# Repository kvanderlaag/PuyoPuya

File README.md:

# PuyoPuya
 Puya MCU Protoboard

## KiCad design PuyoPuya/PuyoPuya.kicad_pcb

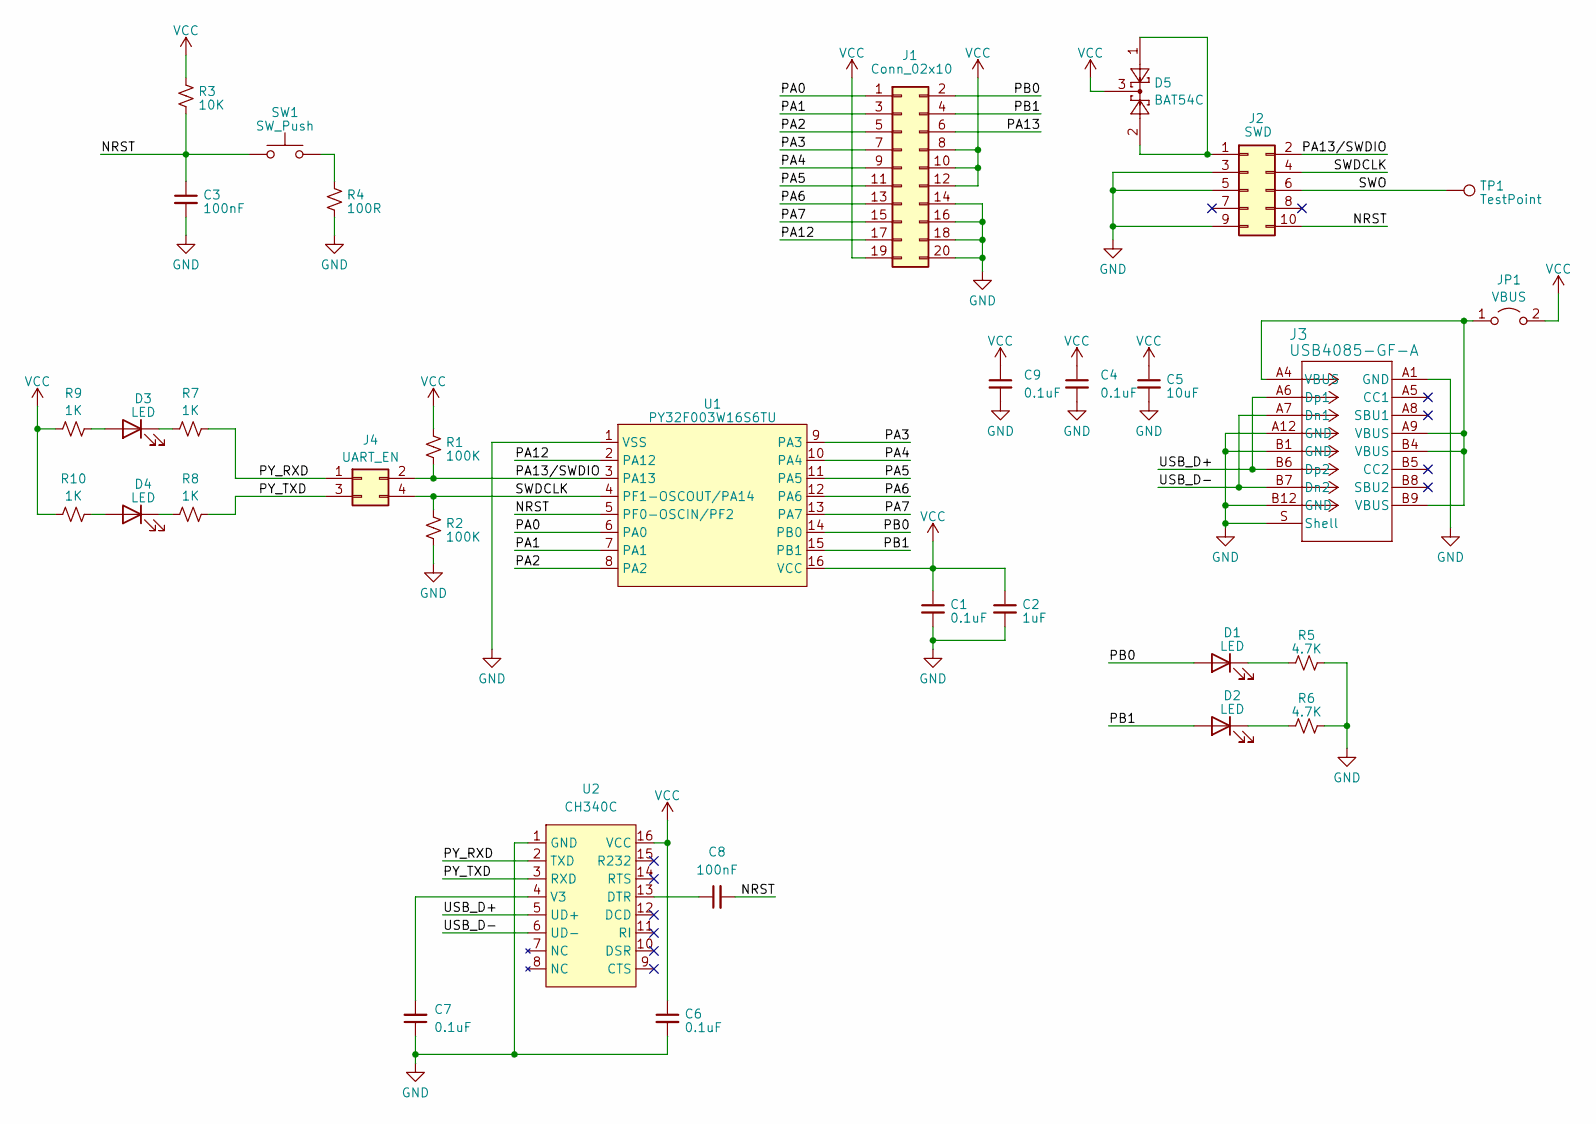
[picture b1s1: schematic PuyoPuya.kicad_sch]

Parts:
C1, C4, C6, C7, C9: 0.1uF; C_0805_2012Metric_Pad1.18x1.45mm_HandSolder
C2: 1uF; C_0805_2012Metric_Pad1.18x1.45mm_HandSolder
C3, C8: 100nF; C_0805_2012Metric_Pad1.18x1.45mm_HandSolder
C5: 10uF; C_0805_2012Metric_Pad1.18x1.45mm_HandSolder
D1, D2, D3, D4: LED; LED_0805_2012Metric_Pad1.15x1.40mm_HandSolder
D5: BAT54C; SOT-23
J1: Conn_02x10; PinSocket_2x10_P2.54mm_Vertical
J2: SWD; PinHeader_2x05_P2.54mm_Vertical
J3: USB4085-GF-A; CONN16_USB4085-GF-A_GCT
J4: UART_EN; PinHeader_2x02_P2.54mm_Vertical
JP1: VBUS; PinHeader_1x02_P2.54mm_Vertical
R1, R2: 100K; R_0805_2012Metric_Pad1.20x1.40mm_HandSolder
R3: 10K; R_0805_2012Metric_Pad1.20x1.40mm_HandSolder
R4: 100R; R_0805_2012Metric_Pad1.20x1.40mm_HandSolder
R5, R6: 4.7K; R_0805_2012Metric_Pad1.20x1.40mm_HandSolder
R7, R8, R9, R10: 1K; R_0805_2012Metric_Pad1.20x1.40mm_HandSolder
SW1: SW_Push; SW4_PTS815 SJM 250 SMTR LFS_CNK
TP1: TestPoint; TestPoint_Pad_D1.5mm
U1: PY32F003W16S6TU; SO-16_3.9x9.9mm_P1.27mm
U2: CH340C; SOP-16_3.9x9.9mm_P1.27mm

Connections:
/NRST: C3.1, C8.2, J2.10, R3.2, SW1.1, U1.5 (PF0-OSCIN/PF2)
/PA0: J1.1, U1.6 (PA0)
/PA1: J1.3, U1.7 (PA1)
/PA2: J1.5, U1.8 (PA2)
/PA3: J1.7, U1.9 (PA3)
/PA4: J1.9, U1.10 (PA4)
/PA5: J1.11, U1.11 (PA5)
/PA6: J1.13, U1.12 (PA6)
/PA7: J1.15, U1.13 (PA7)
/PA12: J1.17, U1.2 (PA12)
/PA13: J1.6
/PA13/SWDIO: J2.2, J4.2, R1.2, U1.3 (PA13)
/PB0: D1.2 (A), J1.2, U1.14 (PB0)
/PB1: D2.2 (A), J1.4, U1.15 (PB1)
/PY_RXD: J4.1, R7.1, U2.2 (TXD)
/PY_TXD: J4.3, R8.1, U2.3 (RXD)
/SWDCLK: J2.4, J4.4, R2.1, U1.4 (PF1-OSCOUT/PA14)
/SWO: J2.6, TP1.1
/USB_D+: J3.A6 (Dp1), J3.B6 (Dp2), U2.5 (UD+)
/USB_D-: J3.A7 (Dn1), J3.B7 (Dn2), U2.6 (UD-)
GND: C1.2, C2.2, C3.2, C4.2, C5.2, C6.2, C7.1, C9.2, J1.14, J1.16, J1.18, J1.20, J2.3, J2.5, J2.9, J3.A1 (GND), J3.A12 (GND), J3.B1 (GND), J3.B12 (GND), J3.S (Shell), R2.2, R4.2, R5.1, R6.1, U1.1 (VSS), U2.1 (GND)
unnamed: D1.1 (K), R5.2
unnamed: D2.1 (K), R6.2
unnamed: D3.2 (A), R9.1
unnamed: D3.1 (K), R7.2
unnamed: D4.2 (A), R10.1
unnamed: D4.1 (K), R8.2
unnamed: D5.1, D5.2, J2.1
unnamed: J3.A4 (VBUS), J3.A9 (VBUS), J3.B4 (VBUS), J3.B9 (VBUS), JP1.1 (A)
unnamed: R4.1, SW1.2
unnamed: C8.1, U2.13 (DTR)
unnamed: C7.2, U2.4 (V3)
VCC: C1.1, C2.1, C4.1, C5.1, C6.1, C9.1, D5.3, J1.8, J1.10, J1.12, J1.19, JP1.2 (B), R1.1, R3.1, R9.2, R10.2, U1.16 (VCC), U2.16 (VCC)

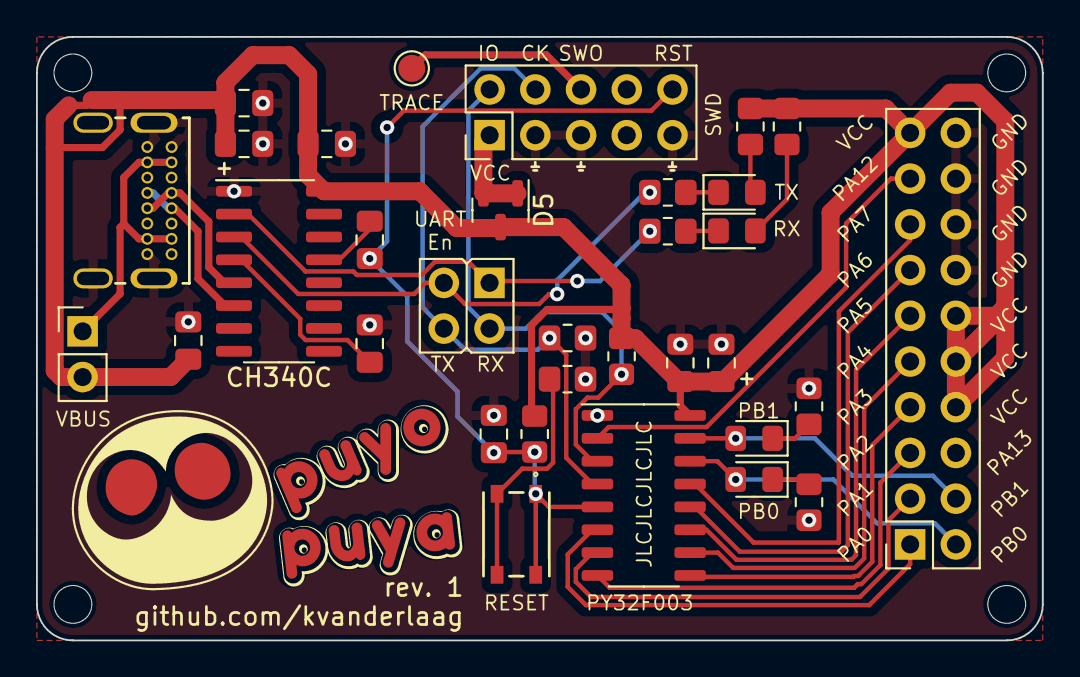
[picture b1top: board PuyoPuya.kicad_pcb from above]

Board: 2 copper layers, 55.9 x 33.5 mm, 33 parts (0 on the bottom side), 32 nets.

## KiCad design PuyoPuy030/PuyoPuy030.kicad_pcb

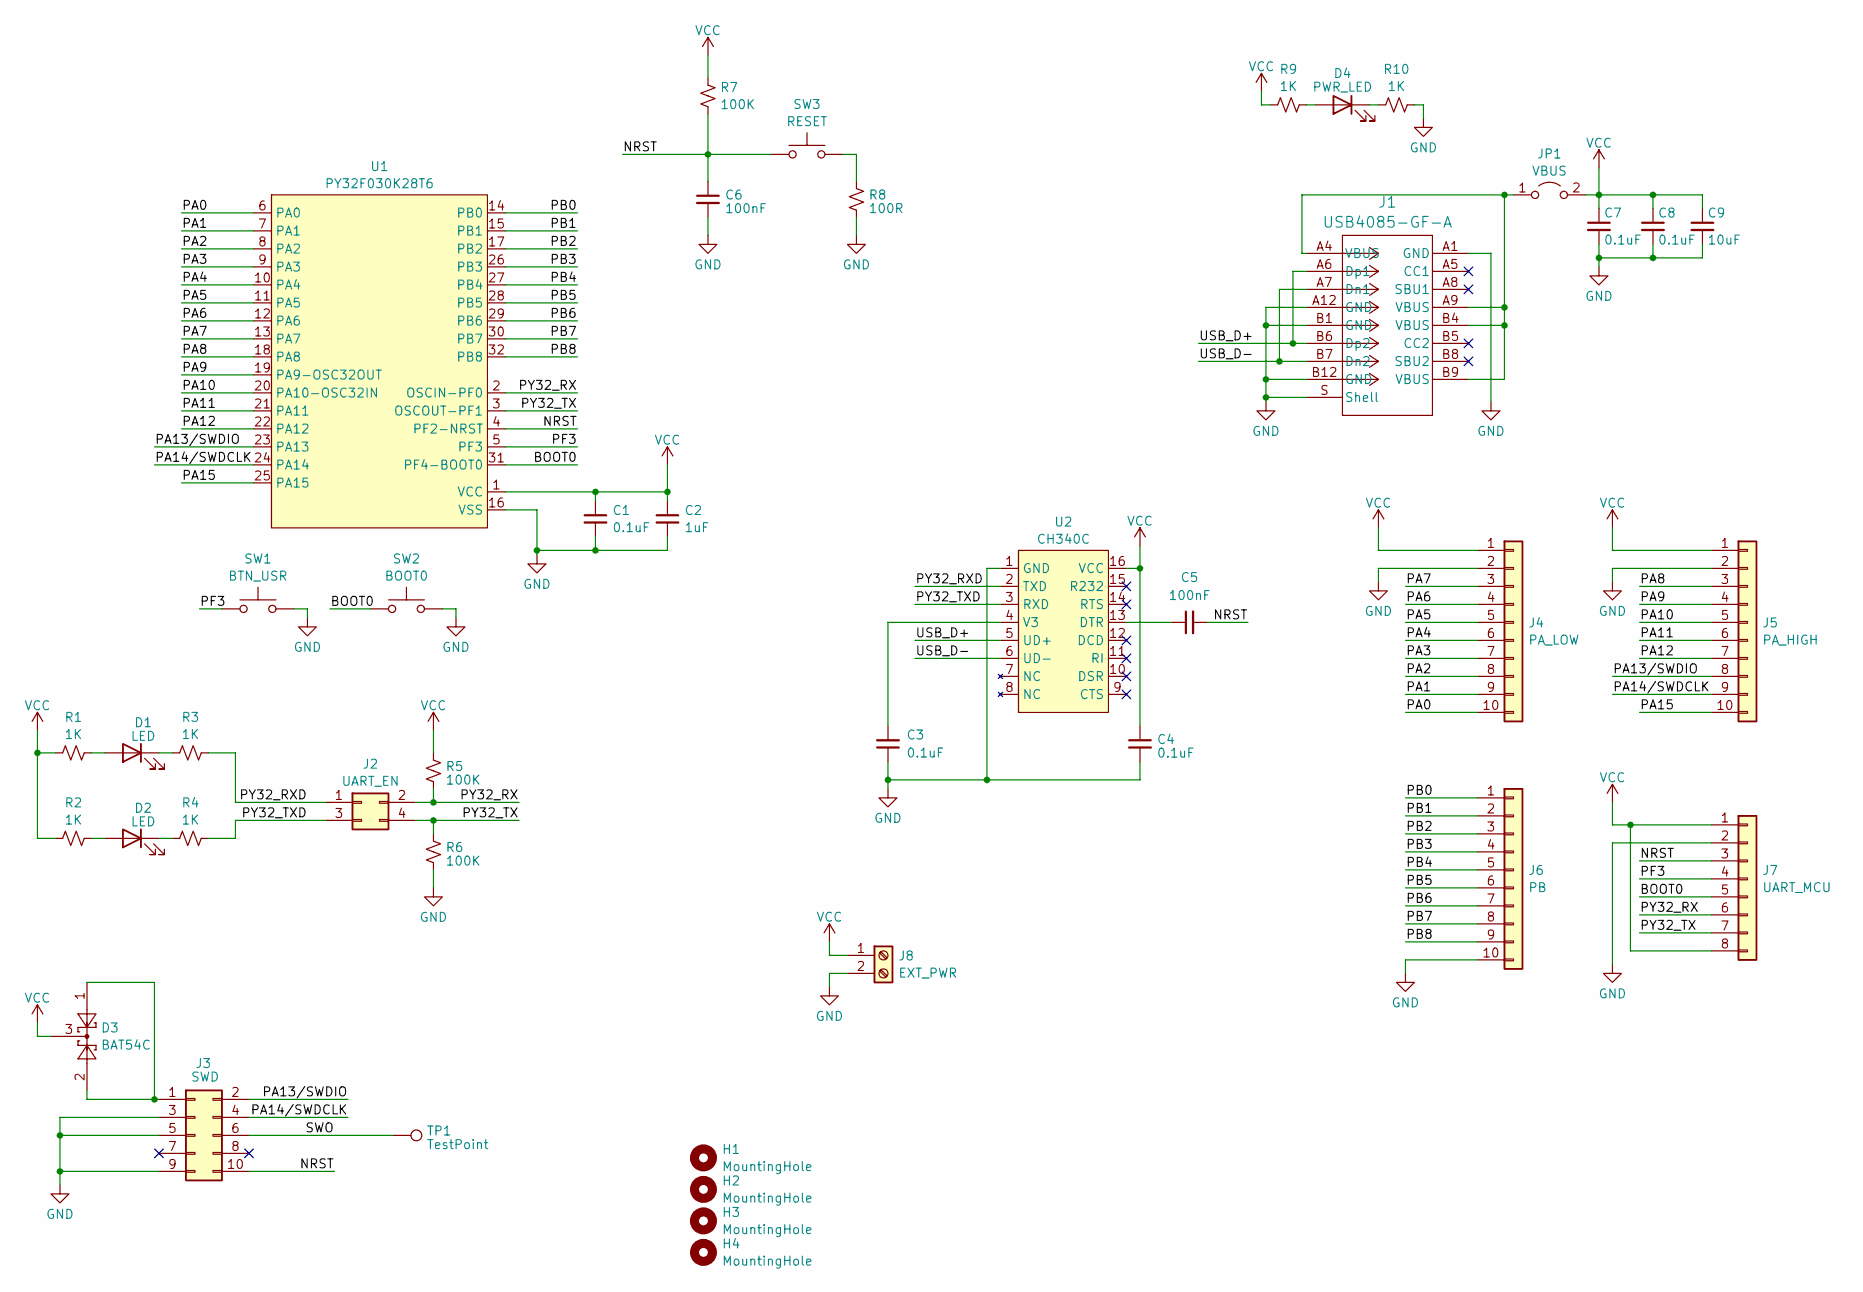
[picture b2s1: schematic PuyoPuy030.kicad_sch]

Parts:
C1, C3, C4, C7, C8: 0.1uF; C_0805_2012Metric
C2: 1uF; C_0805_2012Metric
C5, C6: 100nF; C_0805_2012Metric
C9: 10uF; C_0805_2012Metric
D1, D2: LED; LED_0805_2012Metric_Pad1.15x1.40mm_HandSolder
D3: BAT54C; SOT-23
D4: PWR_LED; LED_0805_2012Metric_Pad1.15x1.40mm_HandSolder
H1, H2, H3, H4: MountingHole; MountingHole_2.2mm_M2
J1: USB4085-GF-A; CONN16_USB4085-GF-A_GCT
J2: UART_EN; PinHeader_2x02_P2.54mm_Vertical
J3: SWD; PinHeader_2x05_P2.54mm_Vertical
J4: PA_LOW; PinSocket_1x10_P2.54mm_Vertical
J5: PA_HIGH; PinSocket_1x10_P2.54mm_Vertical
J6: PB; PinSocket_1x10_P2.54mm_Vertical
J7: UART_MCU; PinSocket_1x08_P2.54mm_Vertical
J8: EXT_PWR; TerminalBlock_TE_282834-2_1x02_P2.54mm_Horizontal
JP1: VBUS; PinHeader_1x02_P2.54mm_Vertical
R1, R2, R3, R4, R9, R10: 1K; R_0805_2012Metric
R5, R6, R7: 100K; R_0805_2012Metric
R8: 100R; R_0805_2012Metric
SW1: BTN_USR; SW4_PTS815 SJM 250 SMTR LFS_CNK
SW2: BOOT0; SW4_PTS815 SJM 250 SMTR LFS_CNK
SW3: RESET; SW4_PTS815 SJM 250 SMTR LFS_CNK
TP1: TestPoint; TestPoint_Pad_D1.5mm
U1: PY32F030K28T6; PY32F030K28T6-LQFP-32_7x7mm_P0.8mm
U2: CH340C; SOP-16_3.9x9.9mm_P1.27mm

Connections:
/BOOT0: J7.5, SW2.1, U1.31 (PF4-BOOT0)
/NRST: C5.2, C6.1, J3.10, J7.3, R7.2, SW3.1, U1.4 (PF2-NRST)
/PA0: J4.10, U1.6 (PA0)
/PA1: J4.9, U1.7 (PA1)
/PA2: J4.8, U1.8 (PA2)
/PA3: J4.7, U1.9 (PA3)
/PA4: J4.6, U1.10 (PA4)
/PA5: J4.5, U1.11 (PA5)
/PA6: J4.4, U1.12 (PA6)
/PA7: J4.3, U1.13 (PA7)
/PA8: J5.3, U1.18 (PA8)
/PA9: J5.4, U1.19 (PA9-OSC32OUT)
/PA10: J5.5, U1.20 (PA10-OSC32IN)
/PA11: J5.6, U1.21 (PA11)
/PA12: J5.7, U1.22 (PA12)
/PA13/SWDIO: J3.2, J5.8, U1.23 (PA13)
/PA14/SWDCLK: J3.4, J5.9, U1.24 (PA14)
/PA15: J5.10, U1.25 (PA15)
/PB0: J6.1, U1.14 (PB0)
/PB1: J6.2, U1.15 (PB1)
/PB2: J6.3, U1.17 (PB2)
/PB3: J6.4, U1.26 (PB3)
/PB4: J6.5, U1.27 (PB4)
/PB5: J6.6, U1.28 (PB5)
/PB6: J6.7, U1.29 (PB6)
/PB7: J6.8, U1.30 (PB7)
/PB8: J6.9, U1.32 (PB8)
/PF3: J7.4, SW1.1, U1.5 (PF3)
/PY32_RX: J2.2, J7.6, R5.2, U1.2 (OSCIN-PF0)
/PY32_RXD: J2.1, R3.1, U2.2 (TXD)
/PY32_TX: J2.4, J7.7, R6.1, U1.3 (OSCOUT-PF1)
/PY32_TXD: J2.3, R4.1, U2.3 (RXD)
/SWO: J3.6, TP1.1
/USB_D+: J1.A6 (Dp1), J1.B6 (Dp2), U2.5 (UD+)
/USB_D-: J1.A7 (Dn1), J1.B7 (Dn2), U2.6 (UD-)
GND: C1.2, C2.2, C3.1, C4.2, C6.2, C7.2, C8.2, C9.2, J1.A1 (GND), J1.A12 (GND), J1.B1 (GND), J1.B12 (GND), J1.S (Shell), J3.3, J3.5, J3.9, J4.2, J5.2, J6.10, J7.2, J8.2, R6.2, R8.2, R10.1, SW1.2, SW2.2, U1.16 (VSS), U2.1 (GND)
unnamed: D1.2 (A), R1.1
unnamed: D1.1 (K), R3.2
unnamed: D2.2 (A), R2.1
unnamed: D2.1 (K), R4.2
unnamed: D4.2 (A), R9.1
unnamed: D4.1 (K), R10.2
unnamed: D3.1, D3.2, J3.1
unnamed: J1.A4 (VBUS), J1.A9 (VBUS), J1.B4 (VBUS), J1.B9 (VBUS), JP1.1 (A)
unnamed: R8.1, SW3.2
unnamed: C5.1, U2.13 (DTR)
unnamed: C3.2, U2.4 (V3)
VCC: C1.1, C2.1, C4.1, C7.1, C8.1, C9.1, D3.3, J4.1, J5.1, J7.1, J7.8, J8.1, JP1.2 (B), R1.2, R2.2, R5.1, R7.1, R9.2, U1.1 (VCC), U2.16 (VCC)

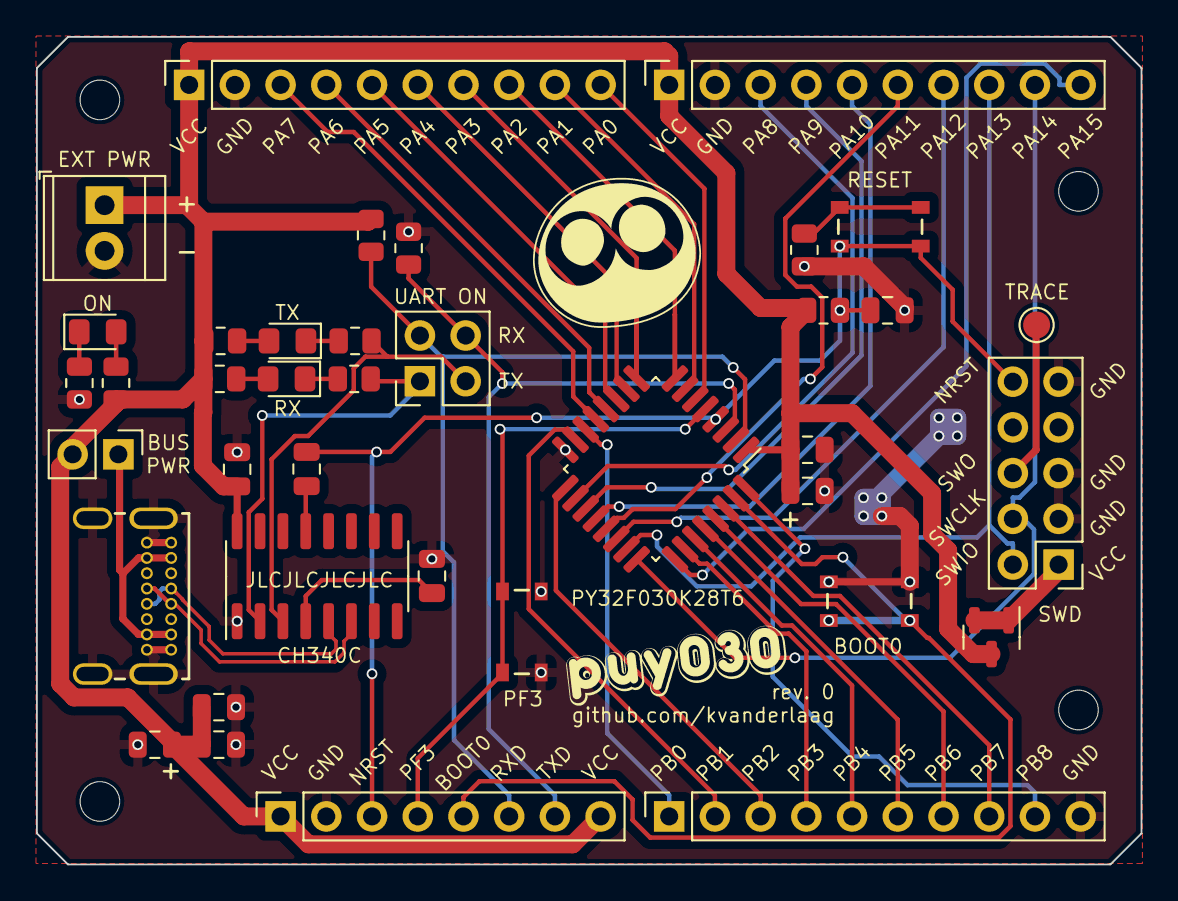
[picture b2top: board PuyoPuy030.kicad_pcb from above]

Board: 2 copper layers, 61.4 x 46.0 mm, 42 parts (0 on the bottom side), 48 nets.

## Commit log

2023-07-08 Boarb
2023-07-10 Fix routing
2023-07-10 CH340C
2023-07-25 PuyoPuy030
2023-07-28 Puyo30
